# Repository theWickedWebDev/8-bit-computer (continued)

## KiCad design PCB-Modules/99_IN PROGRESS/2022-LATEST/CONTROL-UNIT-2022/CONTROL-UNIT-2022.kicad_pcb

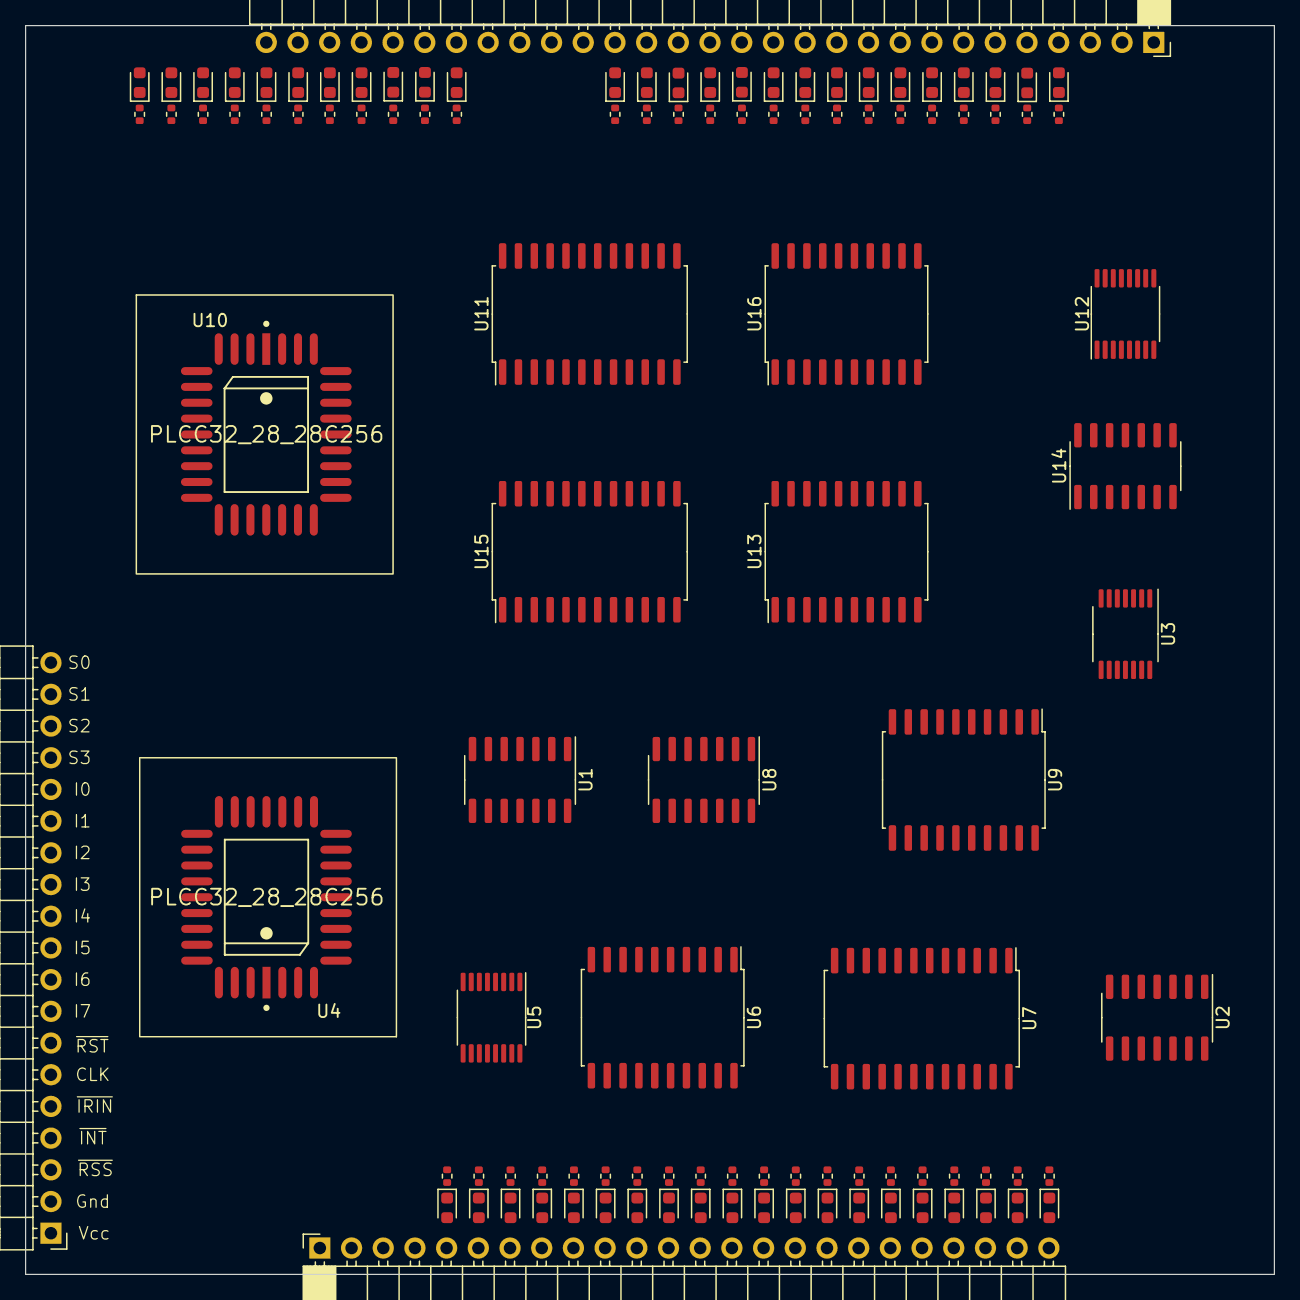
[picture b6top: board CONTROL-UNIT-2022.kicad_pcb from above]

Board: 2 copper layers, 100.1 x 100.1 mm, 111 parts (0 on the bottom side), 143 nets.

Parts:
D1, D2, D3, D4, D5, D6, D7, D8, D9, D10, D11, D12, D13, D14, D15, D16, D17, D18, D19, D20, D21, D22, D23, D24, D25, D26, D27, D28, D29, D30, D31, D32, D33, D34, D35, D36, D37, D38, D39, D40, D41, D42, D43, D44, D45, D46: 19-217/BHC-ZL1M2RY/3T; LED_0603_1608Metric
J1: Conn_01x19; PinHeader_1x19_P2.54mm_Horizontal
J2: Conn_01x24; PinSocket_1x24_P2.54mm_Horizontal
J3: Conn_01x29; PinSocket_1x29_P2.54mm_Horizontal
R1, R2, R3, R4, R5, R6, R7, R8, R9, R10, R11, R12, R13, R14, R15, R16, R17, R18, R19, R20, R21, R22, R23, R24, R25, R26, R27, R28, R29, R30, R31, R32, R33, R34, R35, R36, R37, R38, R39, R40, R41, R42, R43, R44, R45, R46: 0402WGF1001TCE; R_0402_1005Metric
U1, U2, U8, U14: 74LS08; SOIC-14_3.9x8.7mm_P1.27mm
U3: 74LS00; TSSOP-14_4.4x5mm_P0.65mm
U4, U10: PLCC32_28_28C256; PLCC-32-SOCKET-Microchip-32J-10_2001-B-IPC_A
U5, U12: 74LS139; TSSOP-16_4.4x5mm_P0.65mm
U6, U9, U13, U16: 74LS245; SOIC-20W_7.5x12.8mm_P1.27mm
U7, U11, U15: 74LS154; SOIC-24W_7.5x15.4mm_P1.27mm

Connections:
/Destination | Loads/~LATCH_IRQ_PRIORITY: U1.10, U15.5 (S4)
/Destination | Loads/~LATCH_PROGRAM_COUNTER: U1.2, U11.5 (S4)
/Destination | Loads/~WRITE0: U12.4 (O0), U13.19 (CE)
/Destination | Loads/~WRITE1: U12.5 (O1), U15.18 (E0)
/Destination | Loads/~WRITE2: U11.18 (E0), U12.6 (O2)
/Destination | Loads/~cntrl_RESTORE_FLAGS: U14.2, U15.9 (S8)
/Source | Reads (Operand)/~READ0: U5.4 (O0), U6.19 (CE)
/Source | Reads (Operand)/~READ1: U5.5 (O1), U7.18 (E0)
/Source | Reads (Operand)/~READ2: U5.6 (O2), U8.9, U9.6 (A4)
/Source | Reads (Operand)/~READ3: U5.7 (O3), U8.10
/~SOFTWARE_RESET: U2.1, U4.22 (I/O7)
ALU_FUNC_0: D20.2 (A), J3.10, U9.18 (B0)
ALU_FUNC_1: D21.2 (A), J3.9, U9.17 (B1)
ALU_FUNC_2: D22.2 (A), J3.8, U9.16 (B2)
ALU_FUNC_3: D23.2 (A), J3.7, U9.15 (B3)
ALU_FUNC_4: D24.2 (A), J3.6, U9.14 (B4)
ALU_FUNC_5_EN: D25.2 (A), J3.5, U9.13 (B5)
CLOCK: J1.6, J2.3, J3.3
GND: J1.2, J2.2, J3.2, R1.2, R2.2, R3.2, R4.2, R5.2, R6.2, R7.2, R8.2, R9.2, R10.2, R11.2, R12.2, R13.2, R14.2, R15.2, R16.2, R17.2, R18.2, R19.2, R20.2, R21.2, R22.2, R23.2, R24.2, R25.2, R26.2, R27.2, R28.2, R29.2, R30.2, R31.2, R32.2, R33.2, R34.2, R35.2, R36.2, R37.2, R38.2, R39.2, R40.2, R41.2, R42.2, R43.2, R44.2, R45.2, R46.2, U1.7 (GND), U2.7 (GND), U2.12, U2.13, U3.4, U3.5, U3.7 (GND), U3.9, U3.10, U3.12, U3.13, U4.2 (A14), U4.3 (A12), U4.16 (Gnd), U4.23 (~CE), U4.25 (~OE), U4.30 (A14), U5.8 (GND), U5.13 (A1), U5.14 (A0), U6.6 (A4), U6.7 (A5), U6.8 (A6), U6.9 (A7), U6.10 (GND), U7.12 (GND), U7.19 (E1), U8.7 (GND), U8.12, U8.13, U9.8 (A6), U9.9 (A7), U9.10 (GND), U10.2 (A14), U10.3 (A12), U10.16 (Gnd), U10.23 (~CE), U10.25 (~OE), U10.30 (A14), U11.12 (GND), U11.19 (E1), U12.8 (GND), U12.13 (A1), U12.14 (A0), U13.5 (A3), U13.6 (A4), U13.7 (A5), U13.8 (A6), U13.9 (A7), U13.10 (GND), U14.7 (GND), U14.9, U14.10, U14.12, U14.13, U15.12 (GND), U15.19 (E1), U16.6 (A4), U16.7 (A5), U16.8 (A6), U16.9 (A7), U16.10 (GND)
GPR0: D39.2 (A), J2.17, U13.18 (B0)
GPR1: D40.2 (A), J2.18, U13.17 (B1)
GPR2: D41.2 (A), J2.19, U13.16 (B2)
GPR3: D42.2 (A), J2.20, U6.18 (B0)
GPR4: D43.2 (A), J2.21, U6.17 (B1)
GPR5: D44.2 (A), J2.22, U6.16 (B2)
GPR6: D45.2 (A), J2.23, U6.15 (B3)
INST0: J1.15, U4.7 (A4), U10.7 (A4)
INST1: J1.14, U4.6 (A5), U10.6 (A5)
INST2: J1.13, U4.5 (A6), U10.5 (A6)
INST3: J1.12, U4.4 (A7), U10.4 (A7)
INST4: J1.11, U4.29 (A8), U10.29 (A8)
INST5: J1.10, U4.28 (A9), U10.28 (A9)
INST6: J1.9, U4.24 (A10), U10.24 (A10)
INST7: J1.8, U4.27 (A11), U10.27 (A11)
JCC_ADR0: D17.2 (A), J3.13, U16.18 (B0)
JCC_ADR1: D16.2 (A), J3.14, U16.17 (B1)
JCC_ADR2: D15.2 (A), J3.15, U16.16 (B2)
JCC_ADR3: D14.2 (A), J3.16, U16.15 (B3)
JCC_LD_PC_COND: D12.2 (A), J3.18, U1.1
unnamed: D1.1 (K), R1.1
unnamed: D2.1 (K), R2.1
unnamed: D3.1 (K), R3.1
unnamed: D4.1 (K), R4.1
unnamed: D5.1 (K), R5.1
unnamed: D6.1 (K), R6.1
unnamed: D7.1 (K), R7.1
unnamed: D8.1 (K), R8.1
unnamed: D9.1 (K), R9.1
unnamed: D10.1 (K), R10.1
unnamed: D11.1 (K), R11.1
unnamed: D12.1 (K), R12.1
unnamed: D13.1 (K), R13.1
unnamed: D14.1 (K), R14.1
unnamed: D15.1 (K), R15.1
unnamed: D16.1 (K), R16.1
unnamed: D17.1 (K), R17.1
unnamed: D18.1 (K), R18.1
unnamed: D19.1 (K), R19.1
unnamed: D20.1 (K), R20.1
unnamed: D21.1 (K), R21.1
unnamed: D22.1 (K), R22.1
unnamed: D23.1 (K), R23.1
unnamed: D24.1 (K), R24.1
unnamed: D25.1 (K), R25.1
unnamed: D26.1 (K), R26.1
unnamed: D27.1 (K), R27.1
unnamed: D28.1 (K), R28.1
unnamed: D29.1 (K), R29.1
unnamed: D30.1 (K), R30.1
unnamed: D31.1 (K), R31.1
unnamed: D32.1 (K), R32.1
unnamed: D33.1 (K), R33.1
unnamed: D34.1 (K), R34.1
unnamed: D35.1 (K), R35.1
unnamed: D36.1 (K), R36.1
unnamed: D37.1 (K), R37.1
unnamed: D38.1 (K), R38.1
unnamed: D39.1 (K), R39.1
unnamed: D40.1 (K), R40.1
unnamed: D41.1 (K), R41.1
unnamed: D42.1 (K), R42.1
unnamed: D43.1 (K), R43.1
unnamed: D44.1 (K), R44.1
unnamed: D45.1 (K), R45.1
unnamed: D46.1 (K), R46.1
unnamed: U8.3, U8.4
unnamed: U8.8, U9.19 (CE)
RESET: D26.2 (A), D46.2 (A), J2.4, J2.24, J3.4, U3.3
RESTORE_FLAGS: D10.2 (A), J3.20, U14.1, U15.8 (S7)
STEP0: J1.19, U4.11 (A0), U10.11 (A0)
STEP1: J1.18, U4.10 (A1), U10.10 (A1)
STEP2: J1.17, U4.9 (A2), U10.9 (A2)
STEP3: J1.16, U4.8 (A3), U10.8 (A3)
VCC: J1.1, J2.1, J3.1, U1.14 (VCC), U2.14 (VCC), U3.14 (VCC), U4.31 (~WE), U4.32 (Vcc), U5.15 (E), U5.16 (VCC), U6.1 (A->B), U6.20 (VCC), U7.24 (VCC), U8.14 (VCC), U9.1 (A->B), U9.7 (A5), U9.20 (VCC), U10.31 (~WE), U10.32 (Vcc), U11.24 (VCC), U12.15 (E), U12.16 (VCC), U13.1 (A->B), U13.20 (VCC), U14.14 (VCC), U15.24 (VCC), U16.1 (A->B), U16.20 (VCC)
~CODE_SEGMENT_OUT: D32.2 (A), J2.10, U7.4 (S3)
~DATA_SEGMENT_OUT: D35.2 (A), J2.13, U7.5 (S4)
~FLAGS_OUT: D9.2 (A), J3.21, U7.9 (S8)
~IO_READ: U1.4, U7.10 (S9)
~IO_WRITE: U1.5, U15.3 (S2)
~IRQ_READ: U1.12, U7.11 (S10)
~IRQ_REG_SEL: U1.9, U15.4 (S3)
~IRQ_WRITE: U1.8, U1.13
~JCC_EN: D13.2 (A), J3.17, U12.7 (O3), U16.19 (CE)
~LATCH_ACCUMULATOR: D18.2 (A), J3.12, U15.1 (S0)
~LATCH_B: D19.2 (A), J3.11, U15.2 (S1)
~LATCH_CODE_SEGMENT: D30.2 (A), J2.8, U15.13 (S11)
~LATCH_DATA_SEGMENT: D33.2 (A), J2.11, U15.14 (S12)
~LATCH_FLAGS: D11.2 (A), J3.19, U14.3
~LATCH_INSTRUCTION: J1.5, U11.1 (S0)
~LATCH_MAR: D27.2 (A), J2.5, U15.10 (S9)
~LATCH_PROGRAM_COUNTER: D7.2 (A), J3.23, U1.3
~LATCH_STACK_POINTER: D3.2 (A), J3.27, U11.8 (S7)
~LATCH_STACK_SEGMENT: D36.2 (A), J2.14, U15.11 (S10)
~MEM_READ: D28.2 (A), J2.6, U8.6
~MEM_WRITE: D29.2 (A), J2.7, U14.6
~PC_BUS_OUT: D8.2 (A), J3.22, U7.7 (S6)
~PC_DEC: D5.2 (A), J3.25, U11.4 (S3)
~RD_USE_DATA_SEGMENT: U2.5, U7.3 (S2), U8.5
~RD_USE_STACK_SEGMENT: U2.10, U7.1 (S0), U8.1
~RESET: J1.7, U2.3, U3.1, U3.2
~SP_BUS_OUT: D4.2 (A), J3.26, U7.8 (S7)
~SP_DEC: D1.2 (A), J3.29, U11.7 (S6)
~SP_INC: D2.2 (A), J3.28, U11.6 (S5)
~STACK_SEGMENT_OUT: D38.2 (A), J2.16, U7.6 (S5)
~USE_CODE_SEGMENT: D31.2 (A), J2.9, U7.2 (S1), U8.2
~USE_DATA_SEGMENT: D34.2 (A), J2.12, U2.6
~USE_STACK_SEGMENT: D37.2 (A), J2.15, U2.8
~WR_USE_DATA_SEGMENT: U2.4, U14.4, U15.6 (S5)
~WR_USE_STACK_SEGMENT: U2.9, U14.5, U15.7 (S6)
~μResetOp: J1.3, U4.21 (I/O6)
μ0: U10.13 (I/O0), U11.23 (A0), U13.2 (A0), U15.23 (A0), U16.2 (A0)
μ1: U10.14 (I/O1), U11.22 (A1), U13.3 (A1), U15.22 (A1), U16.3 (A1)
μ2: U10.15 (I/O2), U11.21 (A2), U13.4 (A2), U15.21 (A2), U16.4 (A2)
μ3: U10.18 (I/O3), U11.20 (A3), U15.20 (A3), U16.5 (A3)
μ4: U10.19 (I/O4), U12.2 (A0)
μ5: U10.20 (I/O5), U12.3 (A1)
μ8: U4.13 (I/O0), U6.2 (A0), U7.23 (A0), U9.2 (A0)
μ9: U4.14 (I/O1), U6.3 (A1), U7.22 (A1), U9.3 (A1)
μ10: U4.15 (I/O2), U6.4 (A2), U7.21 (A2), U9.4 (A2)
μ11: U4.18 (I/O3), U6.5 (A3), U7.20 (A3), U9.5 (A3)
μ12: U4.19 (I/O4), U5.2 (A0)
μ13: U4.20 (I/O5), U5.3 (A1)
μINC_PC: D6.2 (A), J3.24, U10.22 (I/O7)

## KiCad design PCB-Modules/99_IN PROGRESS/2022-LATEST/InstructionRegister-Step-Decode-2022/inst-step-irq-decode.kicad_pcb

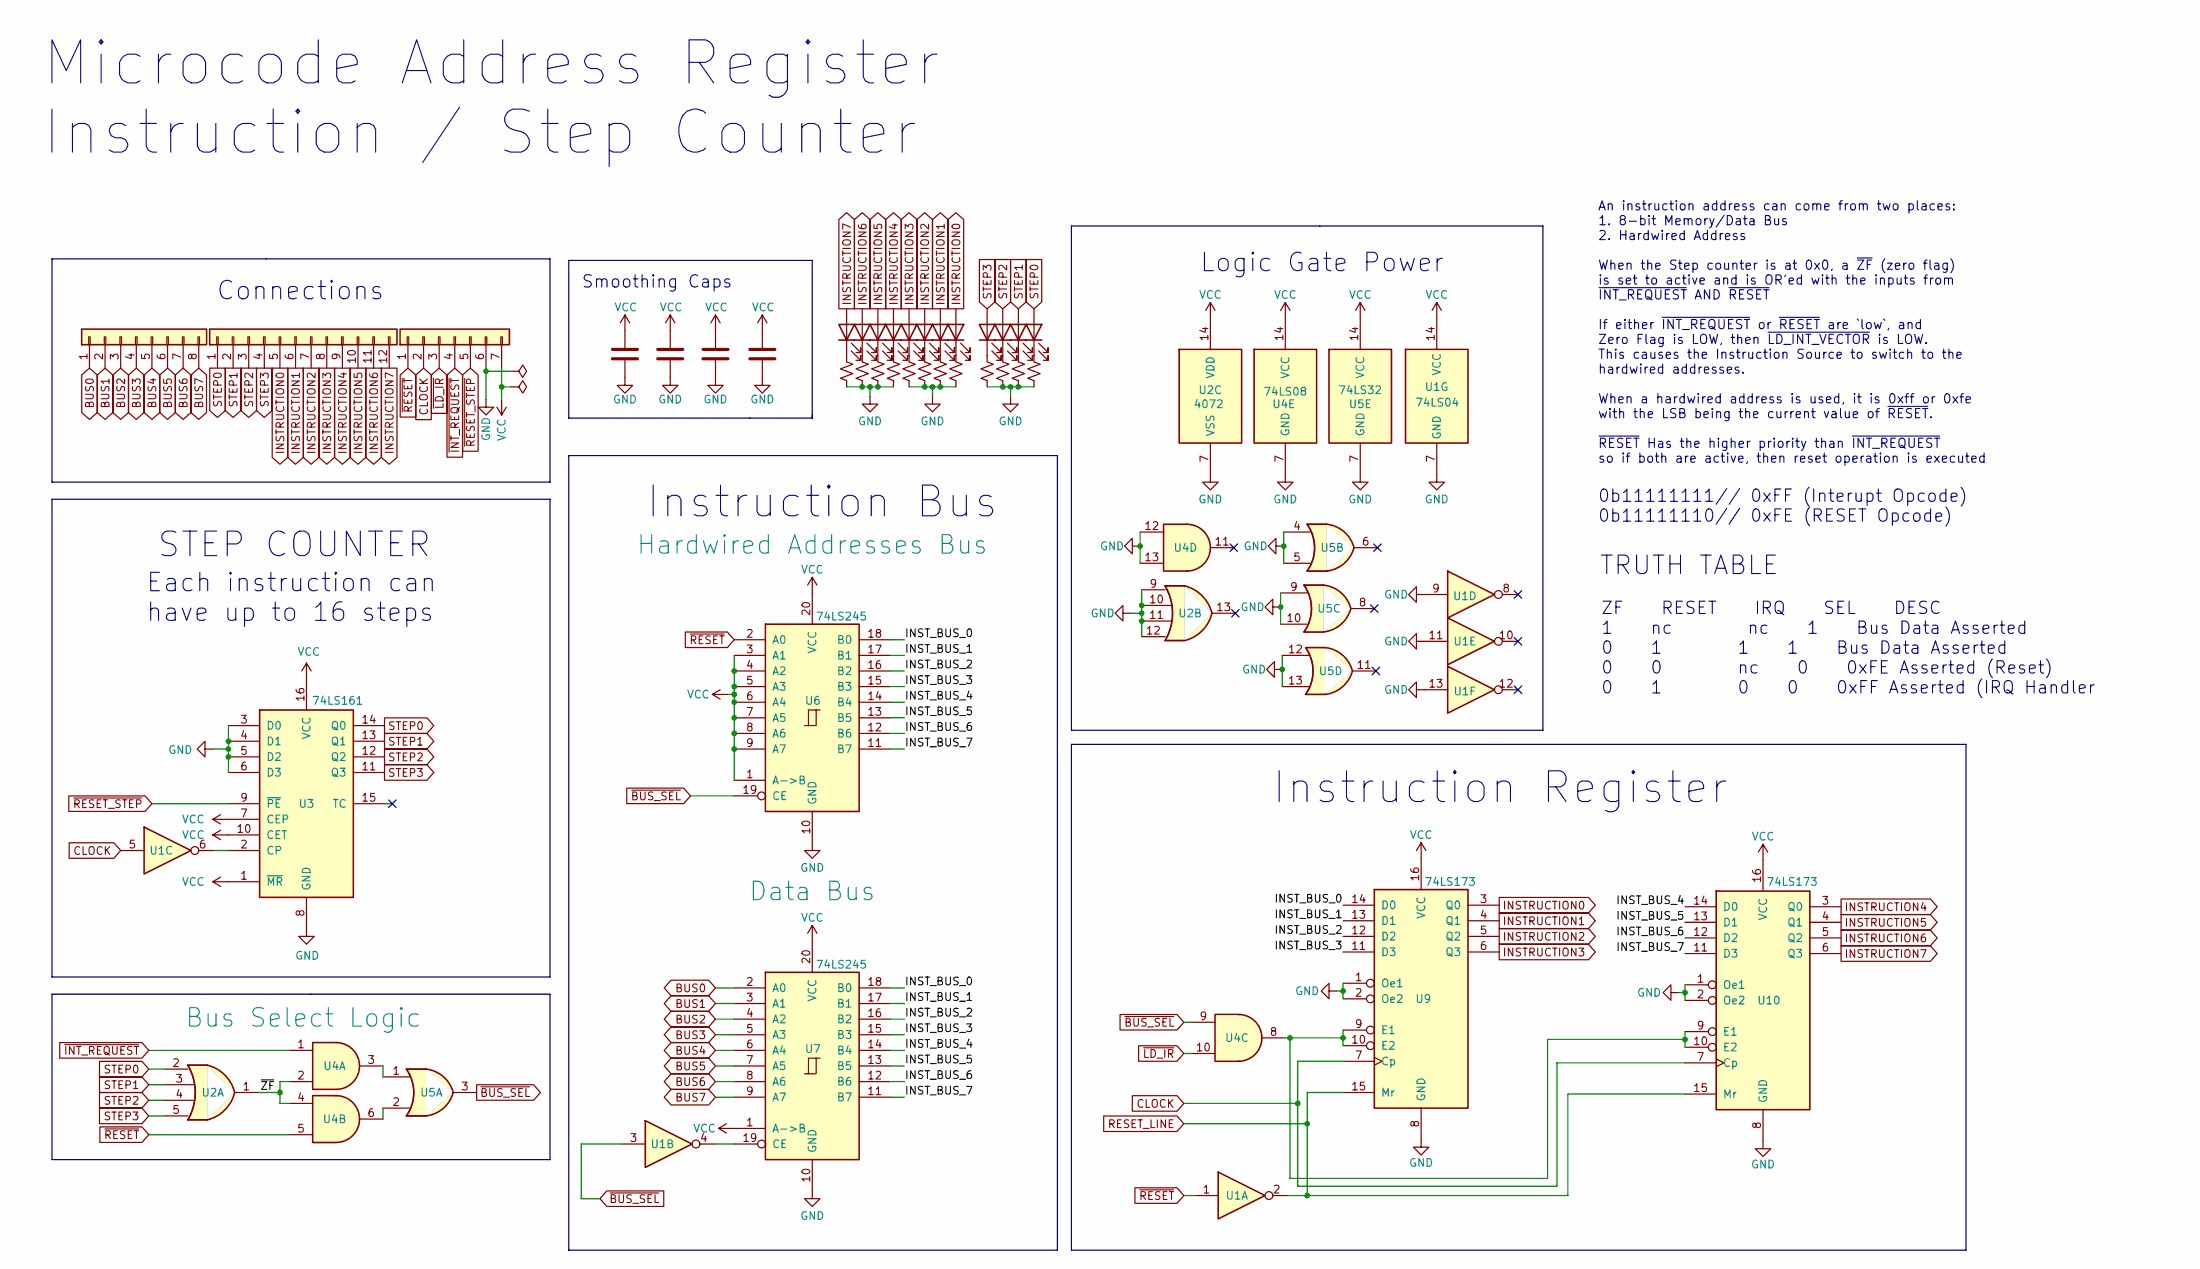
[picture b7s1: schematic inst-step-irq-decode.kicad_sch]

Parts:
C1, C2, C3, C4: C; C_0805_2012Metric
D1, D2, D3, D4, D5, D6, D7, D8, D9, D10, D11, D12: LED; LED_0805_2012Metric
J1: Conn_01x08; PinHeader_1x08_P2.54mm_Vertical
J2: Conn_01x12; PinHeader_1x12_P2.54mm_Vertical
J3: Conn_01x07; PinHeader_1x07_P2.54mm_Vertical
R1, R2, R3, R4, R5, R6, R7, R8, R9, R10, R11, R12: R_Small_US; R_0805_2012Metric
U1: 74LS04; SOIC-14_3.9x8.7mm_P1.27mm
U2: 4072; SOIC-14_3.9x8.7mm_P1.27mm
U3: 74LS161; SOIC-16_3.9x9.9mm_P1.27mm
U4: 74LS08; SOIC-14_3.9x8.7mm_P1.27mm
U5: 74LS32; SOIC-14_3.9x8.7mm_P1.27mm
U6, U7: 74LS245; SOIC-20W_7.5x12.8mm_P1.27mm
U9, U10: 74LS173; SOIC-16_3.9x9.9mm_P1.27mm

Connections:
/INST_BUS_0: U6.18 (B0), U7.18 (B0), U9.14 (D0)
/INST_BUS_1: U6.17 (B1), U7.17 (B1), U9.13 (D1)
/INST_BUS_2: U6.16 (B2), U7.16 (B2), U9.12 (D2)
/INST_BUS_3: U6.15 (B3), U7.15 (B3), U9.11 (D3)
/INST_BUS_4: U6.14 (B4), U7.14 (B4), U10.14 (D0)
/INST_BUS_5: U6.13 (B5), U7.13 (B5), U10.13 (D1)
/INST_BUS_6: U6.12 (B6), U7.12 (B6), U10.12 (D2)
/INST_BUS_7: U6.11 (B7), U7.11 (B7), U10.11 (D3)
/~ZF: U2.1, U4.2, U4.4
BUS0: J1.1, U7.2 (A0)
BUS1: J1.2, U7.3 (A1)
BUS2: J1.3, U7.4 (A2)
BUS3: J1.4, U7.5 (A3)
BUS4: J1.5, U7.6 (A4)
BUS5: J1.6, U7.7 (A5)
BUS6: J1.7, U7.8 (A6)
BUS7: J1.8, U7.9 (A7)
CLOCK: J3.2, U1.5, U9.7 (Cp), U10.7 (Cp)
GND: C1.2, C2.2, C3.2, C4.2, J3.6, R1.2, R2.2, R3.2, R4.2, R5.2, R6.2, R7.2, R8.2, R9.2, R10.2, R11.2, R12.2, U1.7 (GND), U1.9, U1.11, U1.13, U2.7 (VSS), U2.9, U2.10, U2.11, U2.12, U3.3 (D0), U3.4 (D1), U3.5 (D2), U3.6 (D3), U3.8 (GND), U4.7 (GND), U4.12, U4.13, U5.4, U5.5, U5.7 (GND), U5.9, U5.10, U5.12, U5.13, U6.10 (GND), U7.10 (GND), U9.1 (Oe1), U9.2 (Oe2), U9.8 (GND), U10.1 (Oe1), U10.2 (Oe2), U10.8 (GND)
INSTRUCTION0: D8.2 (A), J2.5, U9.3 (Q0)
INSTRUCTION1: D7.2 (A), J2.6, U9.4 (Q1)
INSTRUCTION2: D6.2 (A), J2.7, U9.5 (Q2)
INSTRUCTION3: D5.2 (A), J2.8, U9.6 (Q3)
INSTRUCTION4: D4.2 (A), J2.9, U10.3 (Q0)
INSTRUCTION5: D3.2 (A), J2.10, U10.4 (Q1)
INSTRUCTION6: D2.2 (A), J2.11, U10.5 (Q2)
INSTRUCTION7: D1.2 (A), J2.12, U10.6 (Q3)
unnamed: D1.1 (K), R1.1
unnamed: D2.1 (K), R2.1
unnamed: D3.1 (K), R3.1
unnamed: D4.1 (K), R4.1
unnamed: D5.1 (K), R5.1
unnamed: D6.1 (K), R6.1
unnamed: D7.1 (K), R7.1
unnamed: D8.1 (K), R8.1
unnamed: D9.1 (K), R9.1
unnamed: D10.1 (K), R10.1
unnamed: D11.1 (K), R11.1
unnamed: D12.1 (K), R12.1
unnamed: U1.4, U7.19 (CE)
unnamed: U1.6, U3.2 (CP)
unnamed: U4.3, U5.1
unnamed: U4.6, U5.2
unnamed: U4.8, U9.9 (E1), U9.10 (E2), U10.9 (E1), U10.10 (E2)
RESET_LINE: U1.2, U9.15 (Mr), U10.15 (Mr)
STEP0: D12.2 (A), J2.1, U2.2, U3.14 (Q0)
STEP1: D11.2 (A), J2.2, U2.3, U3.13 (Q1)
STEP2: D10.2 (A), J2.3, U2.4, U3.12 (Q2)
STEP3: D9.2 (A), J2.4, U2.5, U3.11 (Q3)
VCC: C1.1, C2.1, C3.1, C4.1, J3.7, U1.14 (VCC), U2.14 (VDD), U3.1 (~MR), U3.7 (CEP), U3.10 (CET), U3.16 (VCC), U4.14 (VCC), U5.14 (VCC), U6.1 (A->B), U6.3 (A1), U6.4 (A2), U6.5 (A3), U6.6 (A4), U6.7 (A5), U6.8 (A6), U6.9 (A7), U6.20 (VCC), U7.1 (A->B), U7.20 (VCC), U9.16 (VCC), U10.16 (VCC)
~BUS_SEL: U1.3, U4.9, U5.3, U6.19 (CE)
~INT_REQUEST: J3.4, U4.1
~LD_IR: J3.3, U4.10
~RESET_STEP: J3.5, U3.9 (~PE)
~RESET: J3.1, U1.1, U4.5, U6.2 (A0)

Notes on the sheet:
0b11111111// 0xFF (Interupt Opcode) 0b11111110// 0xFE (RESET Opcode)
Each instruction can have up to 16 steps
Connections
An instruction address can come from two places: 1. 8-bit Memory/Data Bus 2. Hardwired Address When the Step counter is at 0x0, a ~{ZF} (zero flag) is set to active and is OR'ed with the inputs from ~{INT_REQUEST} AND ~{RESET} If either ~{INT_REQUEST} or ~{RESET} are `low`, and Zero Flag is LOW, th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
Microcode Address Register Instruction / Step Counter
Logic Gate Power
STEP COUNTER
Instruction Register
Smoothing Caps
Instruction Bus
TRUTH TABLE
ZF RESET IRQ SEL DESC 1 nc nc 1 Bus Data Asserted 0 1 1 1 Bus Data Asserted 0 0 nc 0 0xFE Asserted (Reset) 0 1 0 0 0xFF Asserted (IRQ Handler

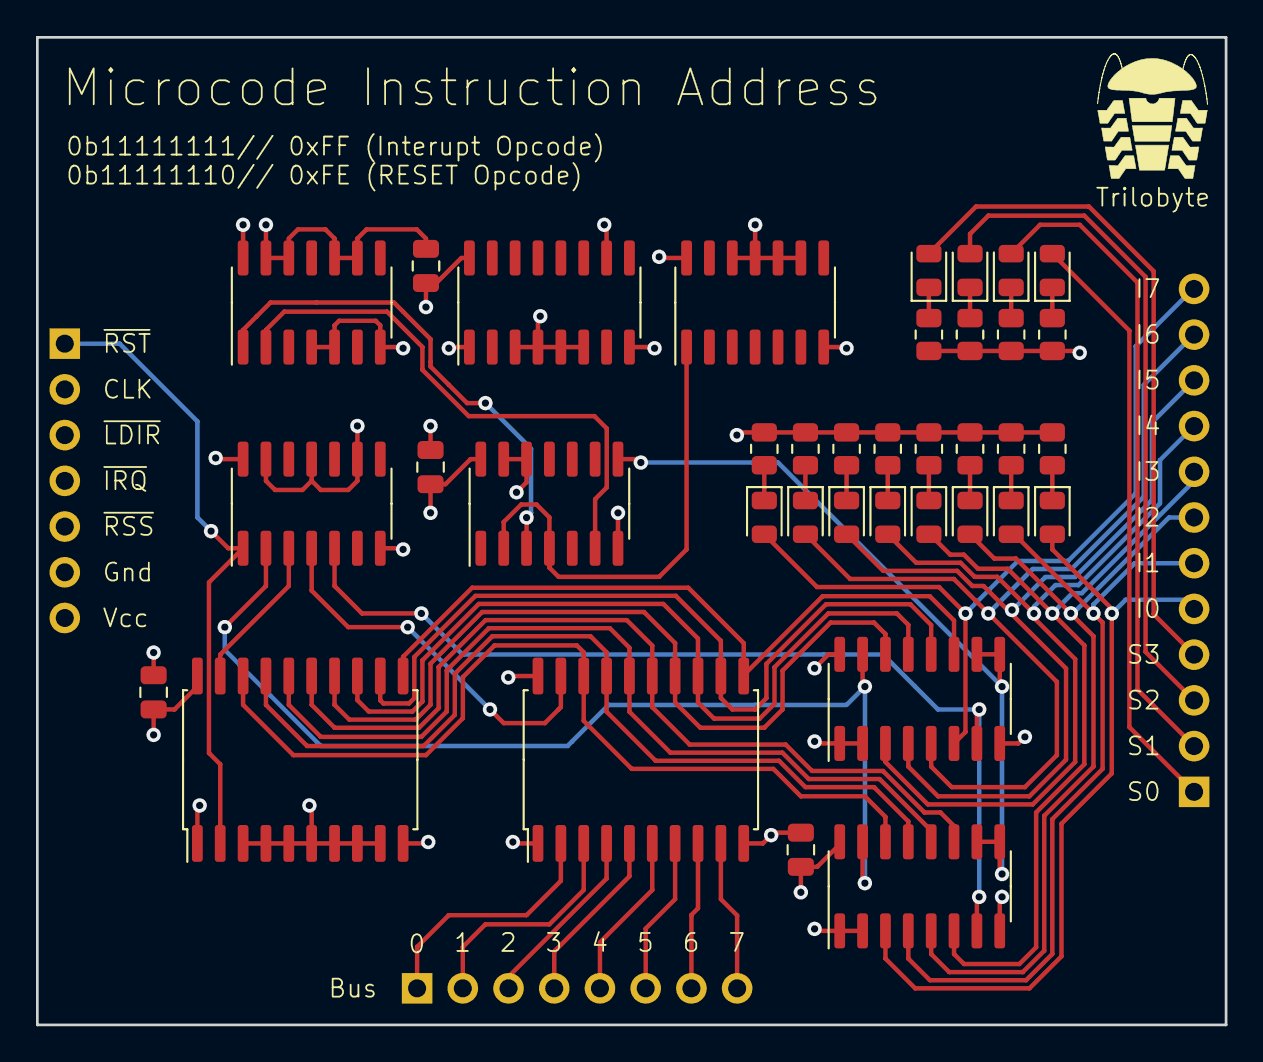
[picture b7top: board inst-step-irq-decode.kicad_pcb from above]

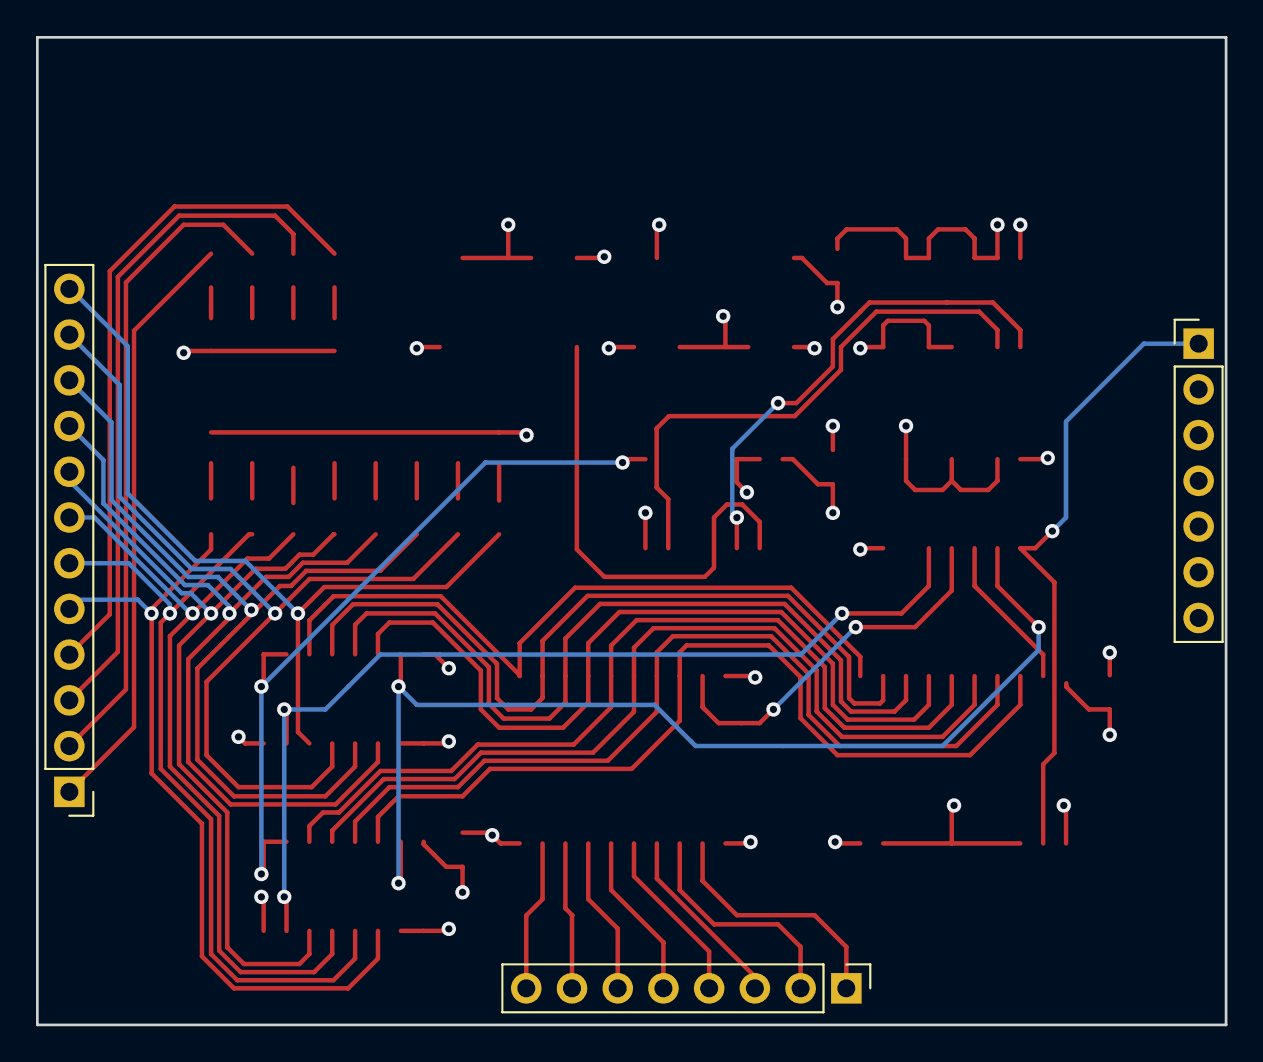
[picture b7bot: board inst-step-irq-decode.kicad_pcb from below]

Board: 4 copper layers, 66.0 x 54.9 mm, 40 parts (3 on the bottom side), 55 nets.
